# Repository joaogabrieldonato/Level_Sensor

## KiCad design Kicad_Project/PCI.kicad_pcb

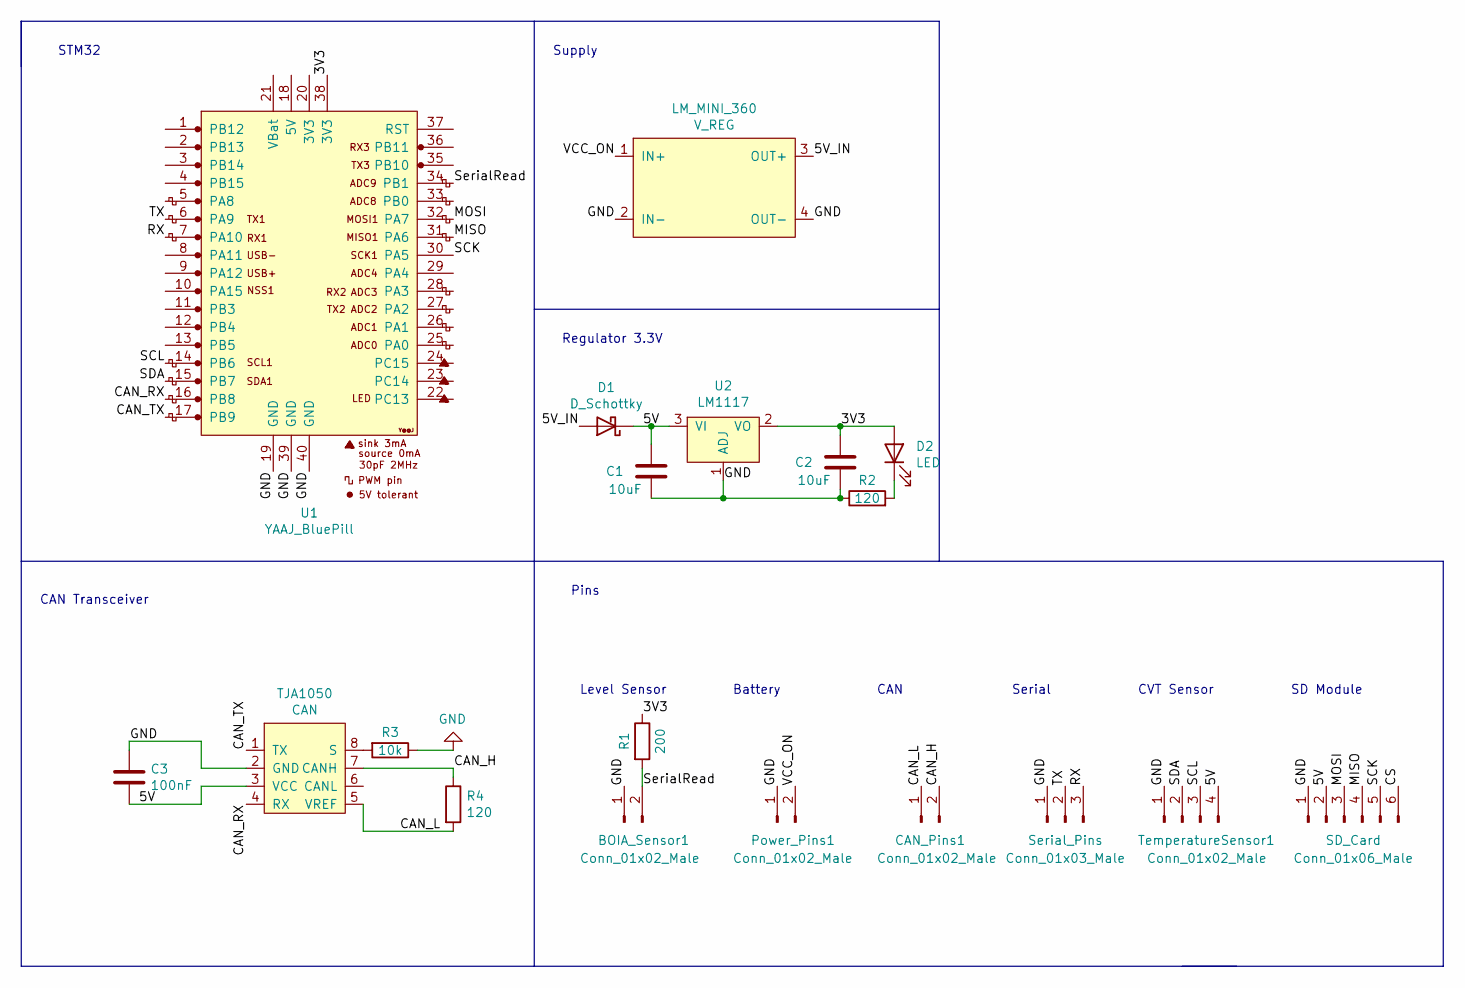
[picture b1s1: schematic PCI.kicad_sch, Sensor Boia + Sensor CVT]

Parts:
BOIA_Sensor1: Conn_01x02_Male; TerminalBlock_bornier-2_P5.08mm
C1, C2: 10uF; C_0805_2012Metric_Pad1.18x1.45mm_HandSolder
C3: 100nF; C_0805_2012Metric_Pad1.18x1.45mm_HandSolder
CAN_Pins1: Conn_01x02_Male; TerminalBlock_bornier-2_P5.08mm
D1: D_Schottky; D_Schotty
D2: LED; D_LED
LM_MINI_360: V_REG; LM2596_DSN_Mini360_Module
Power_Pins1: Conn_01x02_Male; TerminalBlock_bornier-2_P5.08mm
R1: 200; R_0603_1608Metric_Pad0.98x0.95mm_HandSolder
R2: 120; R_0805_2012Metric
R3: 10k; R_0805_2012Metric_Pad1.20x1.40mm_HandSolder
R4: 120; R_0805_2012Metric_Pad1.20x1.40mm_HandSolder
SD_Card: Conn_01x06_Male; TerminalBlock_bornier-6_P5.08mm
Serial_Pins: Conn_01x03_Male; PinHeader_1x03_P2.54mm_Vertical
TJA1050: CAN
TemperatureSensor1: Conn_01x02_Male; TerminalBlock_bornier-4_P5.08mm
U1: YAAJ_BluePill; bluepill
U2: LM1117

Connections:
/3V3: C2.2, D2.2 (A), R1.1, U1.38 (3V3), U2.2 (VO)
/5V: C1.2, C3.2, D1.1 (K), SD_Card.2, TJA1050.3 (VCC), TemperatureSensor1.4, U2.3 (VI)
/5V_IN: D1.2 (A), LM_MINI_360.3 (OUT+)
/CAN_H: CAN_Pins1.2, R4.1, TJA1050.7 (CANH)
/CAN_L: CAN_Pins1.1, R4.2, TJA1050.5 (VREF)
/CAN_RX: TJA1050.4 (RX), U1.16 (PB8)
/CAN_TX: TJA1050.1 (TX), U1.17 (PB9)
/CS: SD_Card.6
/MISO: SD_Card.4, U1.31 (PA6)
/MOSI: SD_Card.3, U1.32 (PA7)
/RX: Serial_Pins.3, U1.7 (PA10)
/SCK: SD_Card.5, U1.30 (PA5)
/SCL: TemperatureSensor1.3, U1.14 (PB6)
/SDA: TemperatureSensor1.2, U1.15 (PB7)
/SerialRead: BOIA_Sensor1.2, R1.2, U1.34 (PB1)
/TX: Serial_Pins.2, U1.6 (PA9)
/VCC_ON: LM_MINI_360.1 (IN+), Power_Pins1.2
GND: BOIA_Sensor1.1, C1.1, C2.1, C3.1, LM_MINI_360.2 (IN-), LM_MINI_360.4 (OUT-), Power_Pins1.1, R2.1, R3.1, SD_Card.1, Serial_Pins.1, TJA1050.2 (GND), TemperatureSensor1.1, U1.19 (GND), U1.39 (GND), U1.40 (GND), U2.1 (ADJ)
unnamed: D2.1 (K), R2.2
unnamed: R3.2, TJA1050.8 (S)

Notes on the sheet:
Serial
CAN
SD Module
Battery
CAN Transceiver
Regulator 3.3V
Pins
CVT Sensor
Level Sensor
Supply
STM32

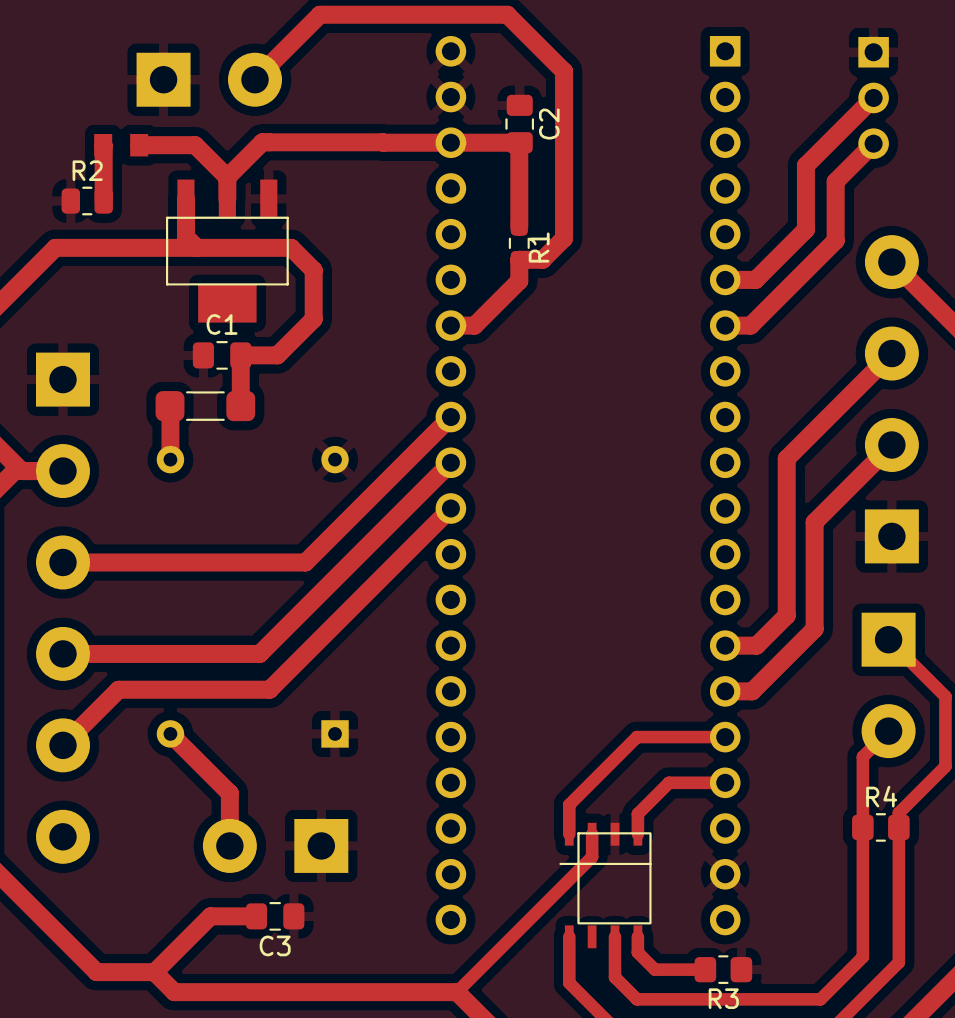
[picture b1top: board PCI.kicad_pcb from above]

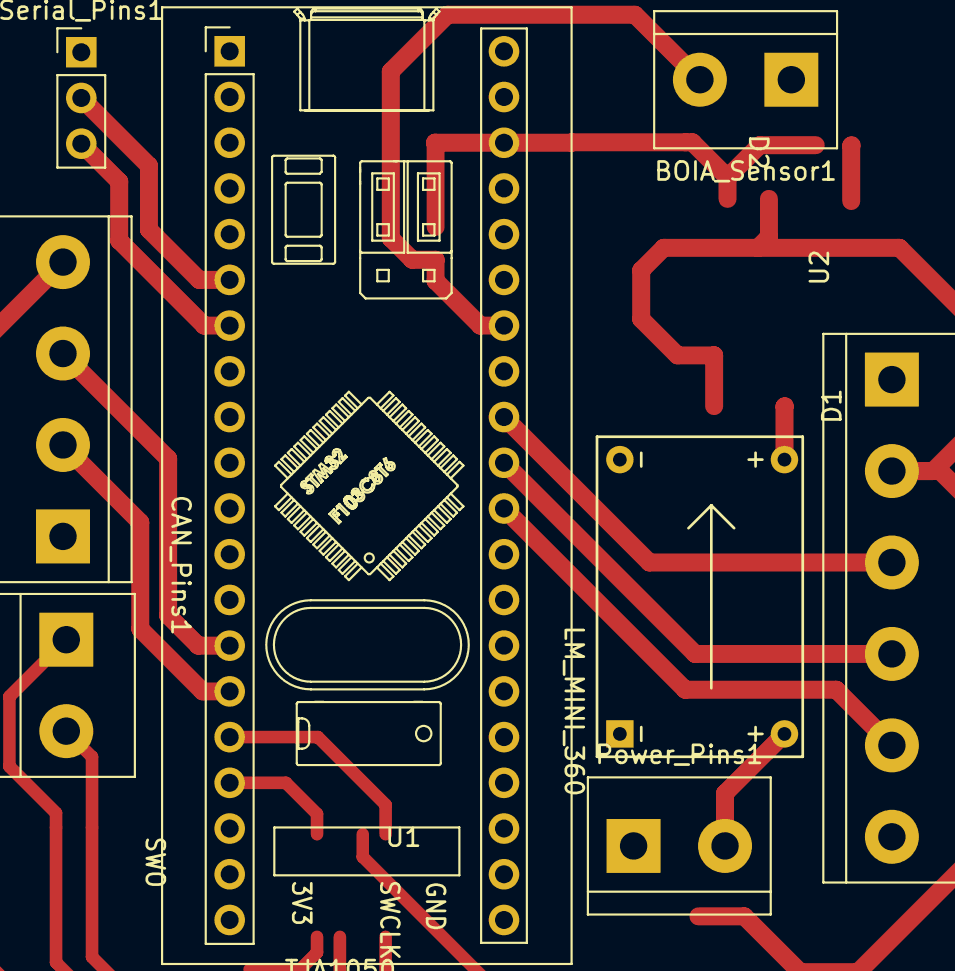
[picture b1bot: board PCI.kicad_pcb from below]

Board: 2 copper layers, 19 parts (12 on the bottom side), 19 nets.
